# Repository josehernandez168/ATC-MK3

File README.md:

# ATC MK3

This repository includes design files and code for the Autonomous Toy Car MK3.
This small rover like robot has capabilities for recognizing objects using a
camera and a Raspberry Pi computer. Furthermore, this vehicle could be
remote controlled through the network by using the Flask library. Check the
report for more details.

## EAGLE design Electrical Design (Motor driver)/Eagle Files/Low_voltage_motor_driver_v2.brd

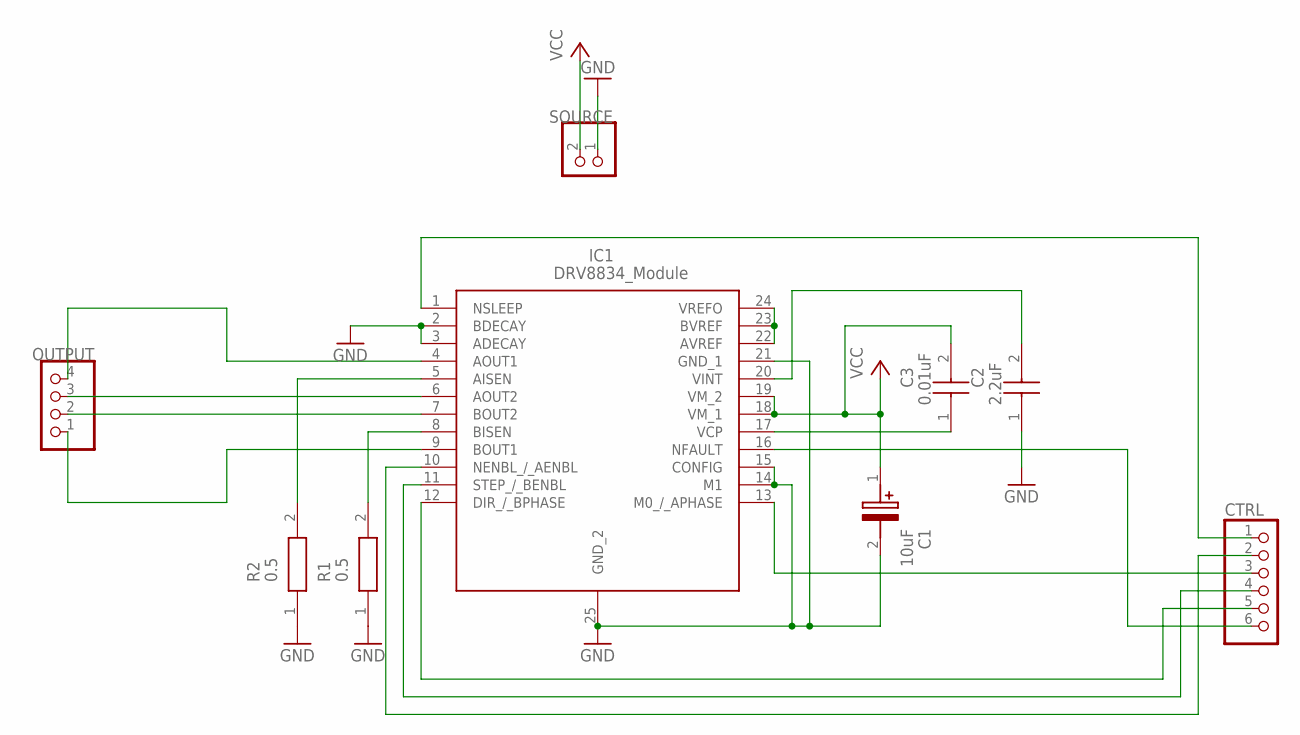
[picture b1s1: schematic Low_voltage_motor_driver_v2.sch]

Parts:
C1: 10uF; CAPPRD200W50D500H1250
C2: 2.2uF; CAPC2012X88N
C3: 0.01uF; CAPC2012X88N
CTRL: PINHD-1X6; 1X06
IC1: DRV8834_Module; SOP65P640X120-25N
OUTPUT: PINHD-1X4; 1X04
R1, R2: 0.5; RESC5125X89N
SOURCE: PINHD-1X2; 1X02

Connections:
GND: C1.2 (-), C2.1, IC1.2 (BDECAY), IC1.3 (ADECAY), IC1.14 (M1), IC1.15 (CONFIG), IC1.21 (GND_1), IC1.25 (GND_2), R1.1, R2.1, SOURCE.1
unnamed: IC1.4 (AOUT1), OUTPUT.4
unnamed: IC1.6 (AOUT2), OUTPUT.3
unnamed: IC1.7 (BOUT2), OUTPUT.2
unnamed: IC1.9 (BOUT1), OUTPUT.1
unnamed: C3.1, IC1.17 (VCP)
unnamed: IC1.22 (AVREF), IC1.23 (BVREF), IC1.24 (VREFO)
unnamed: C2.2, IC1.20 (VINT)
unnamed: IC1.5 (AISEN), R2.2
unnamed: IC1.8 (BISEN), R1.2
unnamed: CTRL.6, IC1.16 (NFAULT)
unnamed: CTRL.1, IC1.1 (NSLEEP)
unnamed: CTRL.2, IC1.10 (NENBL_/_AENBL)
unnamed: CTRL.3, IC1.13 (M0_/_APHASE)
unnamed: CTRL.4, IC1.11 (STEP_/_BENBL)
unnamed: CTRL.5, IC1.12 (DIR_/_BPHASE)
VCC: C1.1 (+), C3.2, IC1.18 (VM_1), IC1.19 (VM_2), SOURCE.2

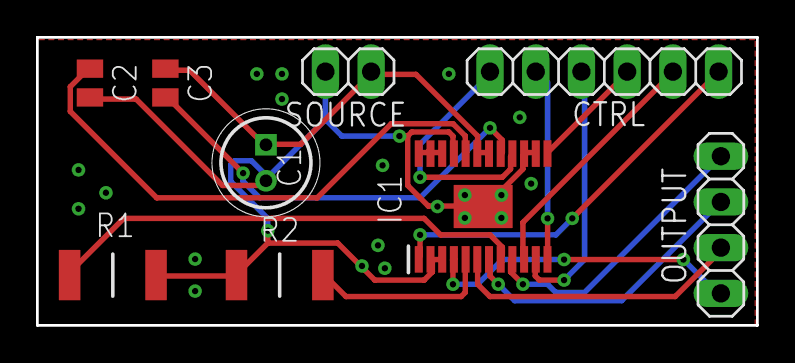
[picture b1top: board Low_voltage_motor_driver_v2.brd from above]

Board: 2 copper layers, 40.0 x 16.0 mm, 9 parts (0 on the bottom side), 17 nets.

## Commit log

2022-09-20 Create Mechanical Design
